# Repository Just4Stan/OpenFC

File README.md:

# OpenFC

Open-source Betaflight flight controller with integrated break-off ELRS receiver, based on the RP2354A microcontroller.

## Features

### Microcontroller
- **RP2354B** - Raspberry Pi dual-core ARM Cortex-M33 @ 150MHz (with integrated flash)

### Integrated ELRS Receiver (Break-off)
- On-board 2.4GHz ExpressLRS receiver module
- Break-off design allows for different placement if needed

### Sensors
- **IMU**: LSM6DSV16XTR 
- **Barometer**: BMI388

### Blackbox Data Logging
- **W25Q128JVPIQTR** - 128Mbit (16MB)

### Motor Outputs
- 4x PWM/DShot motor outputs

### Analog OSD on PIO
Hardware implementation of opamp and mux to detect syncs and select between white and black pixels. Needs software implementation still.

### Connectivity
- **USB-C** - Configuration and firmware flashing
- **UART0** - Serial RX/TX (ELRS connection pads)
- **UART1** - Spare serial port
- **PIO UART** - Software UART via RP2350 PIO (2x)
- **I2C** - External sensor expansion
- **SPI** - IMU and Blackbox on isolated bus.

### Analog Inputs
- Current sensor input (ADC)
- RSSI input (ADC)
- 1 external available ADC input

### Additional Features
- Addressable LED strip output (WS2812/NeoPixel)
- Buzzer output
- 16 LED's built in on corners
- ELRS ESP flashable by the RP2354B (BOOT/EN pins connected)

### Power
- 2S-6S batteries
- 10V and 5V regulated outputs, 10V is switchable.

## Repository Structure

```
OpenFC/
├── README.md
├── .gitignore
├── hardware/          ← KiCad project, libraries, and production files
│   ├── OpenFC.kicad_pro
│   ├── *.kicad_sch    ← Hierarchical schematics
│   ├── OpenFC.kicad_pcb
│   ├── lib.kicad_sym  ← Custom symbol library
│   ├── lib.pretty/    ← Custom footprint library
│   ├── lib.3dshapes/  ← 3D models
│   ├── production/    ← Gerbers, BOM, positions (all versions)
│   └── tools/         ← Analysis scripts
└── images/            ← Board renders
```

## Schematic Hierarchy

- `OpenFC.kicad_sch` - Top-level schematic
- `rp2350a.kicad_sch` - RP2354B microcontroller and supporting circuitry
- `elrs.kicad_sch` - ELRS 2.4GHz receiver module (break-off section)
- `Radioschematic.kicad_sch` - Radio/RF detailed schematic
- `power.kicad_sch` - Power supply and regulation
- `imu.kicad_sch` - LSM6DSV16XTR IMU
- `baro.kicad_sch` - BMP388 barometer
- `compass.kicad_sch` - LIS3MDLTR magnetometer (not populated, but there's space for it)
- `blackbox.kicad_sch` - W25Q128 flash memory
- `leds.kicad_sch` - Status LEDs
- `osd.kicad_sch` - OSD circuitry
- `connectors.kicad_sch` - External connectors
- `pads.kicad_sch` - Solder pads and test points

## Design Files

This project uses **KiCad 9.0** for schematic and PCB design. All symbol, footprint, and 3D model libraries are included in the repository — no external library setup is required.

## License

This project is open-source hardware. See LICENSE file for details.

## Contributing

Contributions are welcome! Please open an issue or submit a pull request.

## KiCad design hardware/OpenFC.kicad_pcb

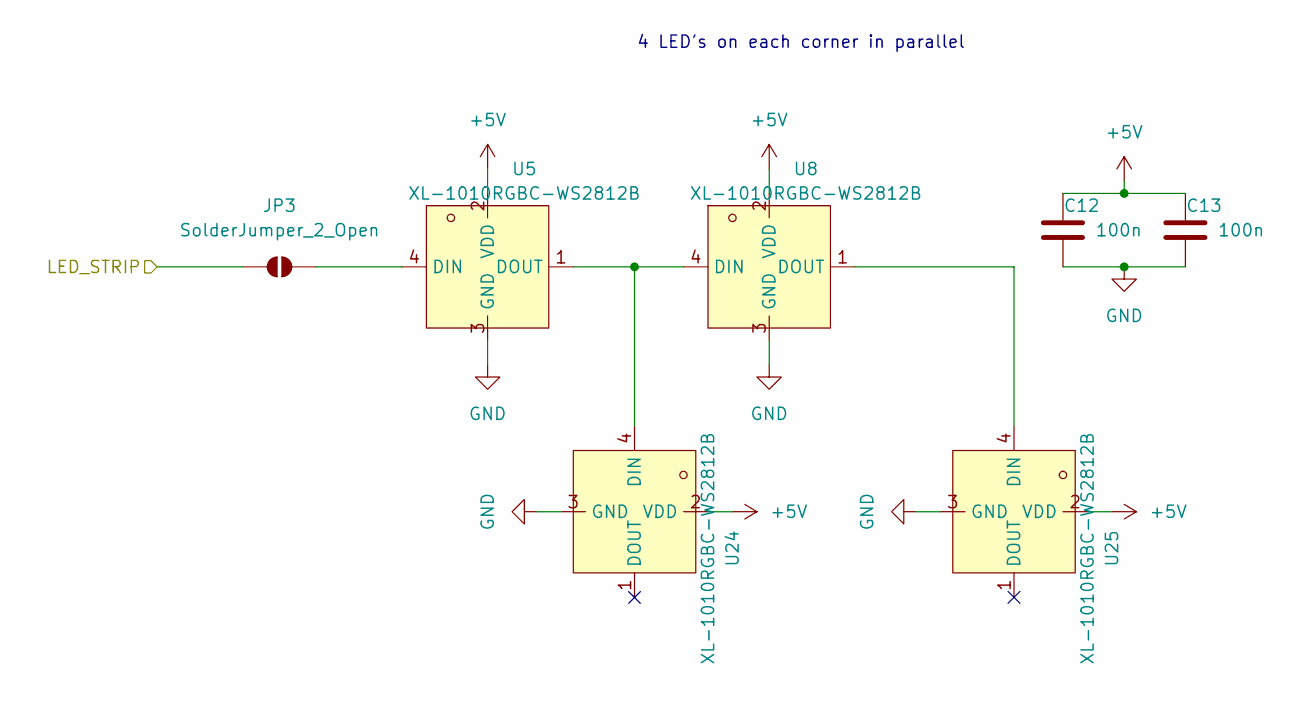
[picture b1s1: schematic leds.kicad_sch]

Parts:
C12, C13: 100n; C_0201_0603Metric; LCSC C76939
JP3: SolderJumper_2_Open; MouseBite-Slot-Jumper_0201
U5, U8, U24, U25: XL-1010RGBC-WS2812B; LED-SMD_4P-L1.0-W1.0-TL_XL-1010RGBC-WS2812B; LCSC Part C5349953

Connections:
+5V: C12.1, C13.1, U5.2 (VDD), U8.2 (VDD), U24.2 (VDD), U25.2 (VDD); also elsewhere on the board
/LED: JP3.1 (A); also elsewhere on the board
unnamed: JP3.2 (B), U5.4 (DIN)
unnamed: U5.1 (DOUT), U8.4 (DIN), U24.4 (DIN)
unnamed: U8.1 (DOUT), U25.4 (DIN)

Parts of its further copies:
C18, C19, C46, C47, C57, C58: 100n; C_0201_0603Metric; LCSC C76939
JP1, JP2, JP4: SolderJumper_2_Open; MouseBite-Slot-Jumper_0201
U3, U4, U15, U16, U17, U18, U22, U23, U26, U27, U28, U29: XL-1010RGBC-WS2812B; LED-SMD_4P-L1.0-W1.0-TL_XL-1010RGBC-WS2812B; LCSC Part C5349953

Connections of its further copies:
+5V: C18.1, C19.1, C46.1, C47.1, C57.1, C58.1, U3.2 (VDD), U4.2 (VDD), U15.2 (VDD), U16.2 (VDD), U17.2 (VDD), U18.2 (VDD), U22.2 (VDD), U23.2 (VDD), U26.2 (VDD), U27.2 (VDD), U28.2 (VDD), U29.2 (VDD); also elsewhere on the board
/LED: JP1.1 (A), JP2.1 (A), JP4.1 (A); also elsewhere on the board
unnamed: JP1.2 (B), U3.4 (DIN)
unnamed: JP2.2 (B), U17.4 (DIN)
unnamed: JP4.2 (B), U26.4 (DIN)
unnamed: U3.1 (DOUT), U4.4 (DIN), U15.4 (DIN)
unnamed: U15.1 (DOUT), U16.4 (DIN)
unnamed: U17.1 (DOUT), U18.4 (DIN), U22.4 (DIN)
unnamed: U22.1 (DOUT), U23.4 (DIN)
unnamed: U26.1 (DOUT), U27.4 (DIN), U28.4 (DIN)
unnamed: U28.1 (DOUT), U29.4 (DIN)

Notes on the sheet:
4 LED's on each corner in parallel

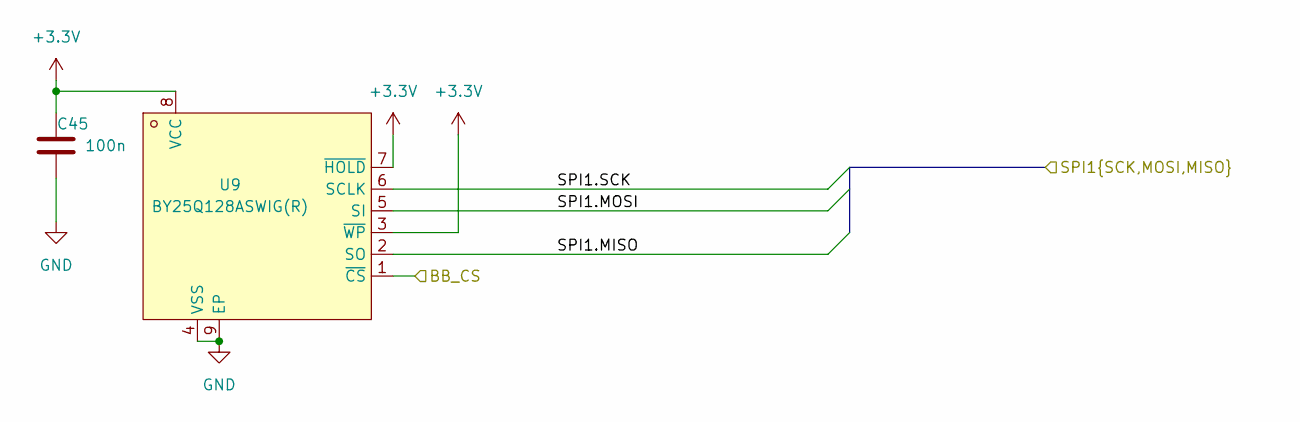
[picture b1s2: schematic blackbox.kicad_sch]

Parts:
C45: 100n; C_0201_0603Metric; LCSC C76939
U9: BY25Q128ASWIG(R); WSON-8_L6.0-W5.0-P1.27-BL-EP; LCSC Part C394872

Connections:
+3.3V: C45.1, U9.3 (~WP), U9.7 (~HOLD), U9.8 (VCC); also elsewhere on the board
/BLACKBOX/BB_CS: U9.1 (~CS); also elsewhere on the board
/BLACKBOX/SPI1.MISO: U9.2 (SO); also elsewhere on the board
/BLACKBOX/SPI1.MOSI: U9.5 (SI); also elsewhere on the board
/BLACKBOX/SPI1.SCK: U9.6 (SCLK); also elsewhere on the board

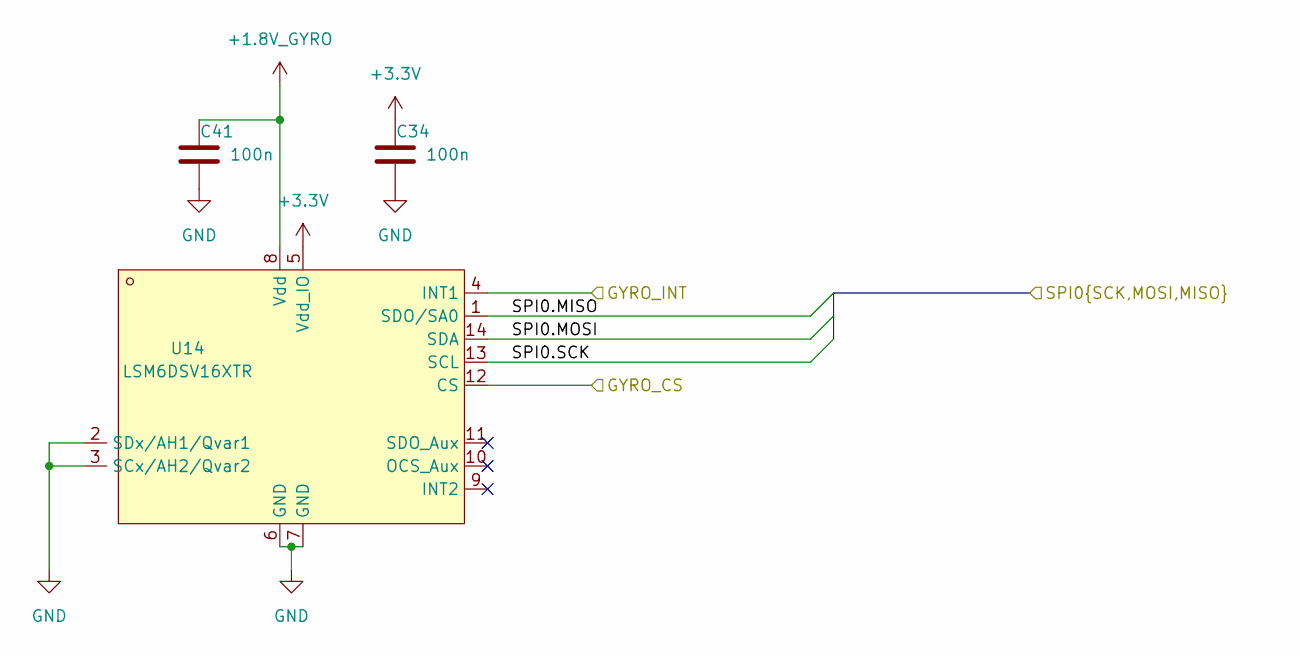
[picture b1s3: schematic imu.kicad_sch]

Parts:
C34, C41: 100n; C_0201_0603Metric; LCSC C76939
U14: LSM6DSV16XTR; LGA-14_L3.0-W2.5-P0.50-BR; LCSC Part C5267406

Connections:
+1.8V_GYRO: C41.1, U14.8 (Vdd); also elsewhere on the board
+3.3V: C34.1, U14.5 (Vdd_IO); also elsewhere on the board
/IMU/GYRO_CS: U14.12 (CS); also elsewhere on the board
/IMU/GYRO_INT: U14.4 (INT1); also elsewhere on the board
/IMU/SPI0.MISO: U14.1 (SDO/SA0); also elsewhere on the board
/IMU/SPI0.MOSI: U14.14 (SDA); also elsewhere on the board
/IMU/SPI0.SCK: U14.13 (SCL); also elsewhere on the board

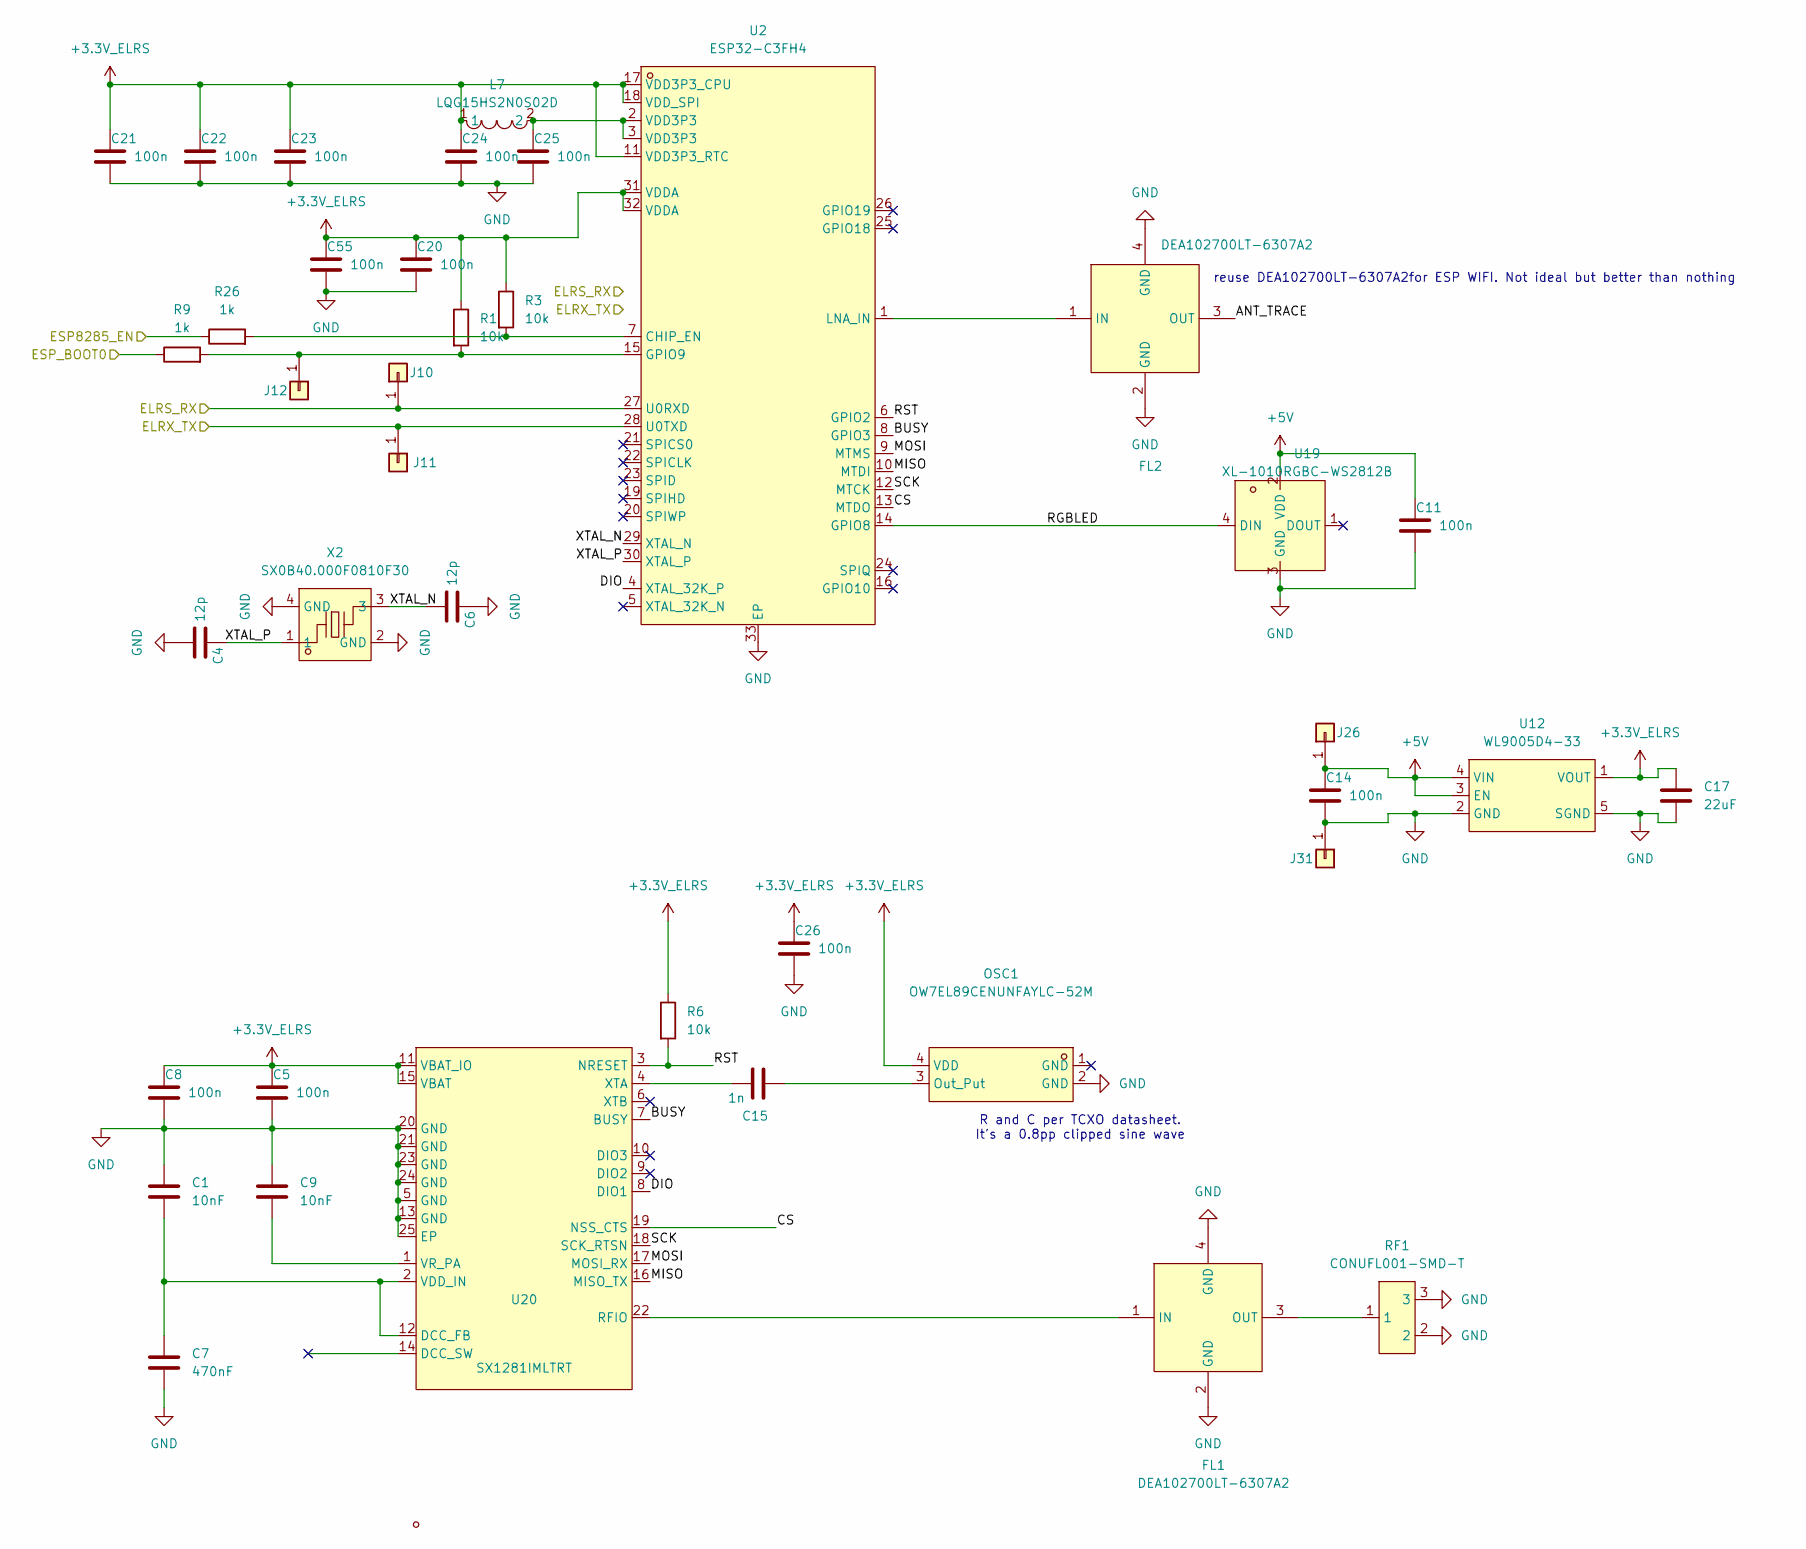
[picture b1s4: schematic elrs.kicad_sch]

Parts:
C1, C9: 10nF; C_0201_0603Metric; LCSC C76941
C4, C6: 12p; C_0201_0603Metric; LCSC C161404
C5, C8, C11, C14, C20, C21, C22, C23, C24, C25, C26, C55: 100n; C_0201_0603Metric; LCSC C76939
C7: 470nF; C_0201_0603Metric; LCSC C85926
C15: 1n; C_0201_0603Metric; LCSC C85934
C17: 22uF; C_0402_1005Metric; LCSC C105226
FL1, FL2: DEA102700LT-6307A2; FILTER-SMD_4P-L1.0-W0.5-L; LCSC Part C574024
J10, J11, J12, J26, J31: 5V; small_pad
L7: LQG15HS2N0S02D; L0402; LCSC Part C18216
OSC1: OW7EL89CENUNFAYLC-52M; OSC-SMD_4P-L2.0-W1.6-BL_TXC_7Z; LCSC Part C22434896
R1, R3, R6: 10k; C_0201_0603Metric; LCSC C473048
R9, R26: 1k; C_0201_0603Metric; LCSC C270365
RF1: CONUFL001-SMD-T; IPEX-SMD_3P-L2.6-W2.6-LS3.0; LCSC Part C22418213
U2: ESP32-C3FH4; QFN-32_L5.0-W5.0-P0.50-TL-EP3.7; LCSC Part C2858491
U12: WL9005D4-33; UDFN-4_L1.0-W1.0-P0.65-TL; LCSC Part C5357206
U19: XL-1010RGBC-WS2812B; LED-SMD_4P-L1.0-W1.0-TL_XL-1010RGBC-WS2812B; LCSC Part C5349953
U20: SX1281IMLTRT; QFN-24_L4.0-W4.0-P0.50-TL-EP2.6; LCSC Part C2151551
X2: SX0B40.000F0810F30; CRYSTAL-SMD_4P-L1.6-W1.2-BL; LCSC Part C7301926

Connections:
+3.3V_ELRS: C5.1, C8.1, C17.1, C20.1, C21.1, C22.1, C23.1, C24.1, C26.1, C55.1, L7.1, OSC1.4 (VDD), R1.1, R3.1, R6.1, U2.11 (VDD3P3_RTC), U2.17 (VDD3P3_CPU), U2.18 (VDD_SPI), U2.31 (VDDA), U2.32 (VDDA), U12.1 (VOUT), U20.11 (VBAT_IO), U20.15 (VBAT)
+5V: C11.1, C14.1, J26.1, U12.3 (EN), U12.4 (VIN), U19.2 (VDD); also elsewhere on the board
/ELRS/ANT_TRACE: FL2.3 (OUT)
/ELRS/BUSY: U2.8 (GPIO3), U20.7 (BUSY)
/ELRS/CS: U2.13 (MTDO), U20.19 (NSS_CTS)
/ELRS/DIO: U2.4 (XTAL_32K_P), U20.8 (DIO1)
/ELRS/ESP8285_EN: R26.1; also elsewhere on the board
/ELRS/ESP_BOOT0: R9.1; also elsewhere on the board
/ELRS/MISO: U2.10 (MTDI), U20.16 (MISO_TX)
/ELRS/MOSI: U2.9 (MTMS), U20.17 (MOSI_RX)
/ELRS/RGBLED: U2.14 (GPIO8), U19.4 (DIN)
/ELRS/RST: R6.2, U2.6 (GPIO2), U20.3 (NRESET)
/ELRS/SCK: U2.12 (MTCK), U20.18 (SCK_RTSN)
/ELRS/XTAL_N: C6.2, U2.29 (XTAL_N), X2.3
/ELRS/XTAL_P: C4.1, U2.30 (XTAL_P), X2.1
/UART1_RX: J11.1, U2.28 (U0TXD); also elsewhere on the board
/UART1_TX: J10.1, U2.27 (U0RXD); also elsewhere on the board
unnamed: C25.1, L7.2, U2.2 (VDD3P3), U2.3 (VDD3P3)
unnamed: FL1.1 (IN), U20.22 (RFIO)
unnamed: FL1.3 (OUT), RF1.1
unnamed: FL2.1 (IN), U2.1 (LNA_IN)
unnamed: J12.1, R1.2, R9.2, U2.15 (GPIO9)
unnamed: C15.2, OSC1.3 (Out_Put)
unnamed: R3.2, R26.2, U2.7 (CHIP_EN)
unnamed: C1.2, C7.1, U20.2 (VDD_IN), U20.12 (DCC_FB)
unnamed: C9.2, U20.1 (VR_PA)
unnamed: C15.1, U20.4 (XTA)

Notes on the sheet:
reuse DEA102700LT-6307A2for ESP WIFI. Not ideal but better than nothing
R and C per TCXO datasheet. It's a 0.8pp clipped sine wave

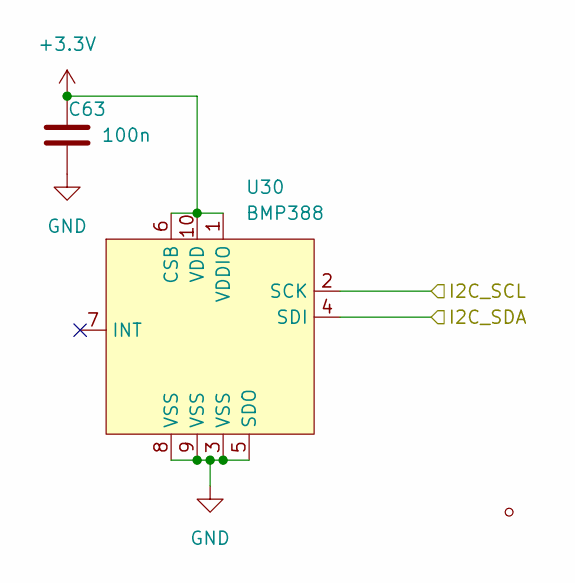
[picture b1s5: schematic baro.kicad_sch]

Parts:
C63: 100n; C_0201_0603Metric; LCSC C76939
U30: BMP388; SENSORM-SMD_BMP388; LCSC Part C779278

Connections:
+3.3V: C63.1, U30.1 (VDDIO), U30.6 (CSB), U30.10 (VDD); also elsewhere on the board
/I2C_SCL: U30.2 (SCK); also elsewhere on the board
/I2C_SDA: U30.4 (SDI); also elsewhere on the board

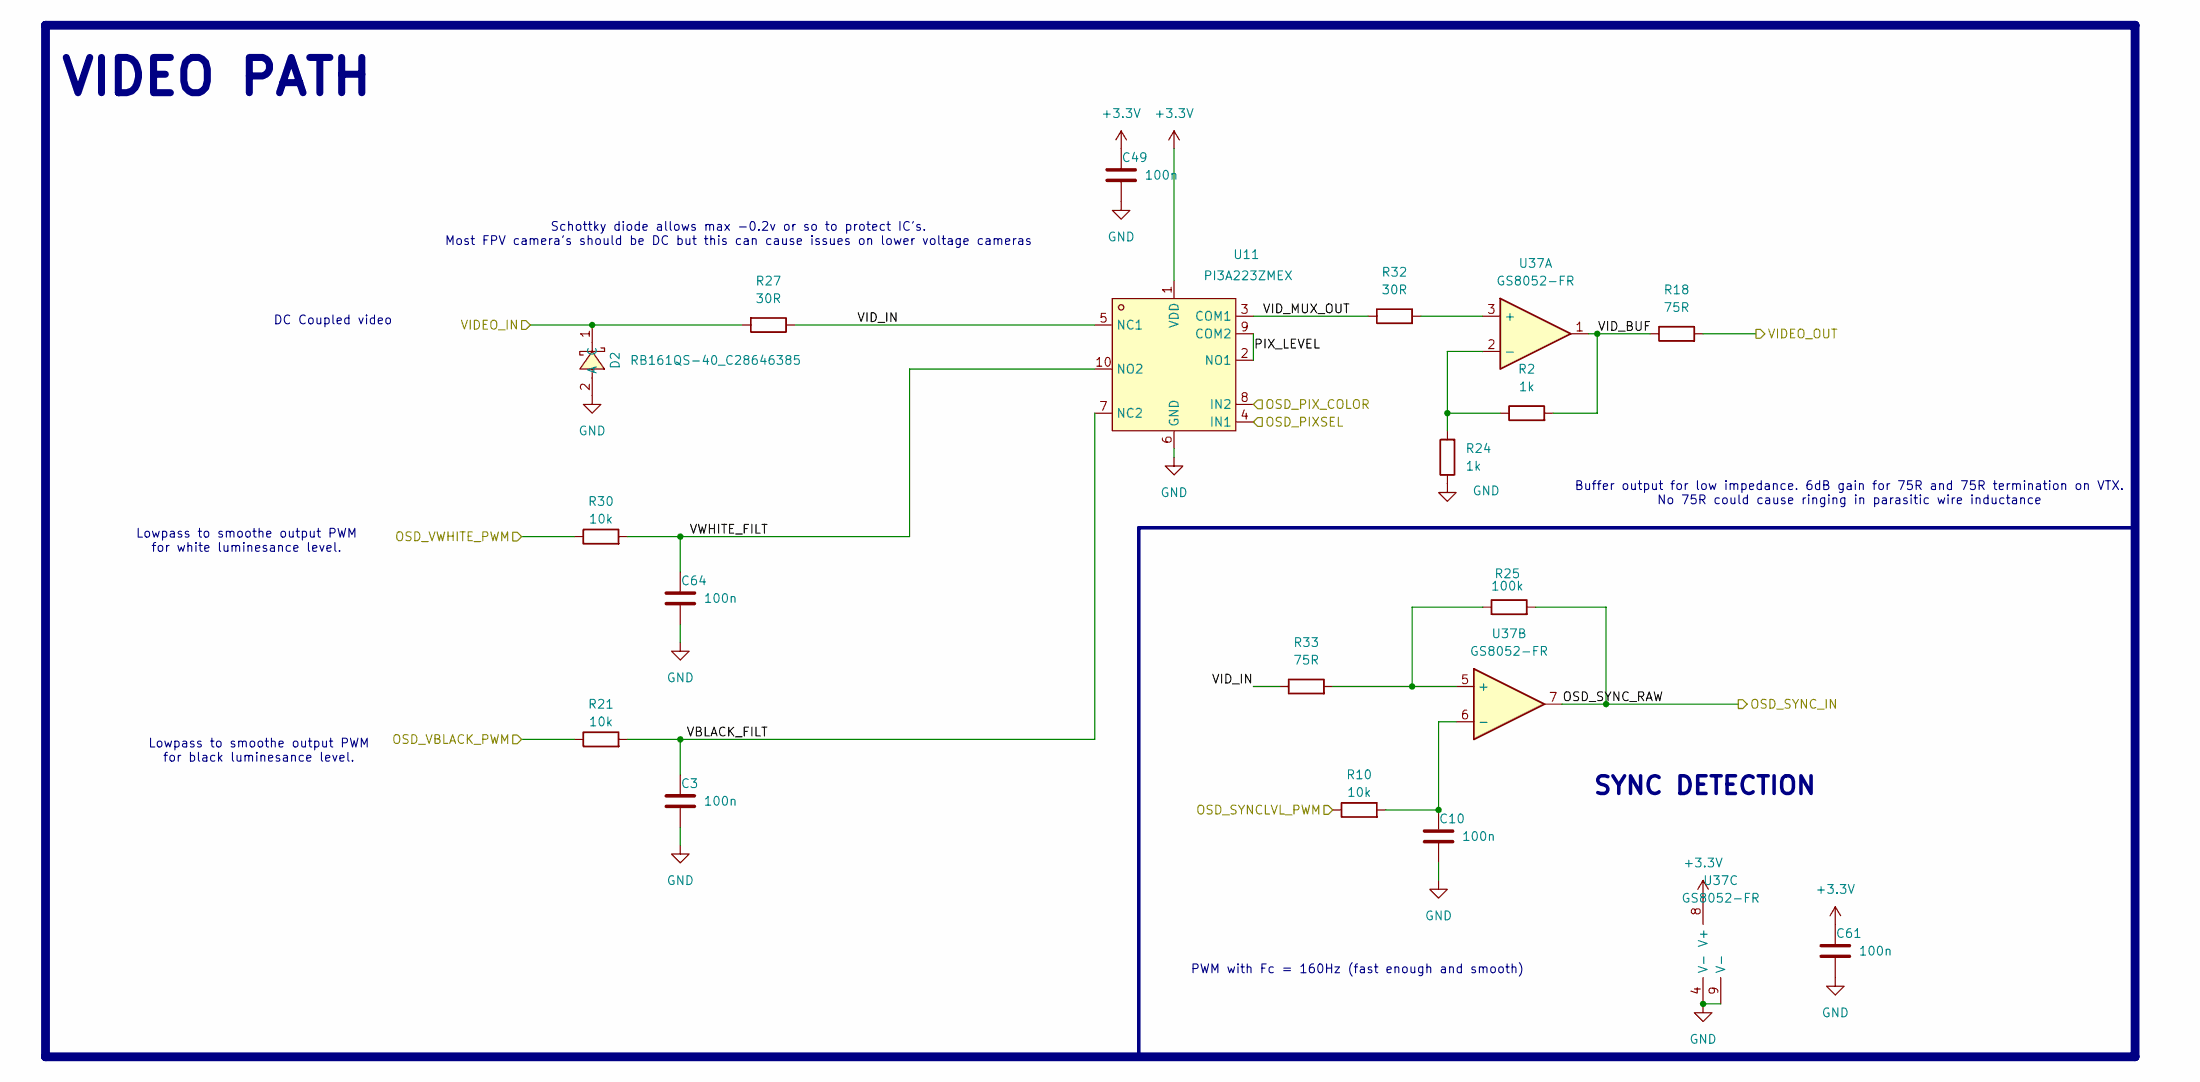
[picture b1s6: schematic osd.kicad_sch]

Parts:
C3, C10, C49, C61, C64: 100n; C_0201_0603Metric; LCSC C76939
D2: RB161QS-40_C28646385; SOD-882_L1.0-W0.6-RD; LCSC Part C28646385
R2, R24: 1k; C_0201_0603Metric; LCSC C270365
R10, R21, R30: 10k; C_0201_0603Metric; LCSC C473048
R18, R33: 75R; C_0201_0603Metric; LCSC C473570
R25: 100k; C_0201_0603Metric; LCSC C270364
R27, R32: 30R; C_0201_0603Metric; LCSC C778391
U11: PI3A223ZMEX; UQFN-10_L1.8-W1.4-P0.40-TL; LCSC Part C2673436
U37: GS8052-FR; WSON-8-1EP_2x2mm_P0.5mm_EP0.9x1.6mm; LCSC C605423

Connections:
+3.3V: C49.1, C61.1, U11.1 (VDD), U37.8 (V+); also elsewhere on the board
/OSD/OSD_PIXSEL: U11.4 (IN1); also elsewhere on the board
/OSD/OSD_PIX_COLOR: U11.8 (IN2); also elsewhere on the board
/OSD/OSD_SYNCLVL_PWM: R10.1; also elsewhere on the board
/OSD/OSD_SYNC_RAW: R25.2, U37.7; also elsewhere on the board
/OSD/OSD_VBLACK_PWM: R21.1; also elsewhere on the board
/OSD/OSD_VWHITE_PWM: R30.1; also elsewhere on the board
/OSD/PIX_LEVEL: U11.2 (NO1), U11.9 (COM2)
/OSD/VBLACK_FILT: C3.1, R21.2, U11.7 (NC2)
/OSD/VIDEO_IN: D2.1 (C), R27.2; also elsewhere on the board
/OSD/VIDEO_OUT: R18.2; also elsewhere on the board
/OSD/VID_BUF: R2.2, R18.1, U37.1
/OSD/VID_IN: R27.1, R33.1, U11.5 (NC1)
/OSD/VID_MUX_OUT: R32.1, U11.3 (COM1)
/OSD/VWHITE_FILT: C64.1, R30.2, U11.10 (NO2)
unnamed: R32.2, U37.3 (+)
unnamed: R2.1, R24.2, U37.2 (-)
unnamed: R25.1, R33.2, U37.5 (+)
unnamed: C10.1, R10.2, U37.6 (-)

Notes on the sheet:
PWM with Fc = 160Hz (fast enough and smooth)
DC Coupled video
Buffer output for low impedance. 6dB gain for 75R and 75R termination on VTX. No 75R could cause ringing in parasitic wire inductance
VIDEO PATH
SYNC DETECTION
Lowpass to smoothe output PWM for white luminesance level.
Lowpass to smoothe output PWM for black luminesance level.
Schottky diode allows max -0.2v or so to protect IC's. Most FPV camera's should be DC but this can cause issues on lower voltage cameras

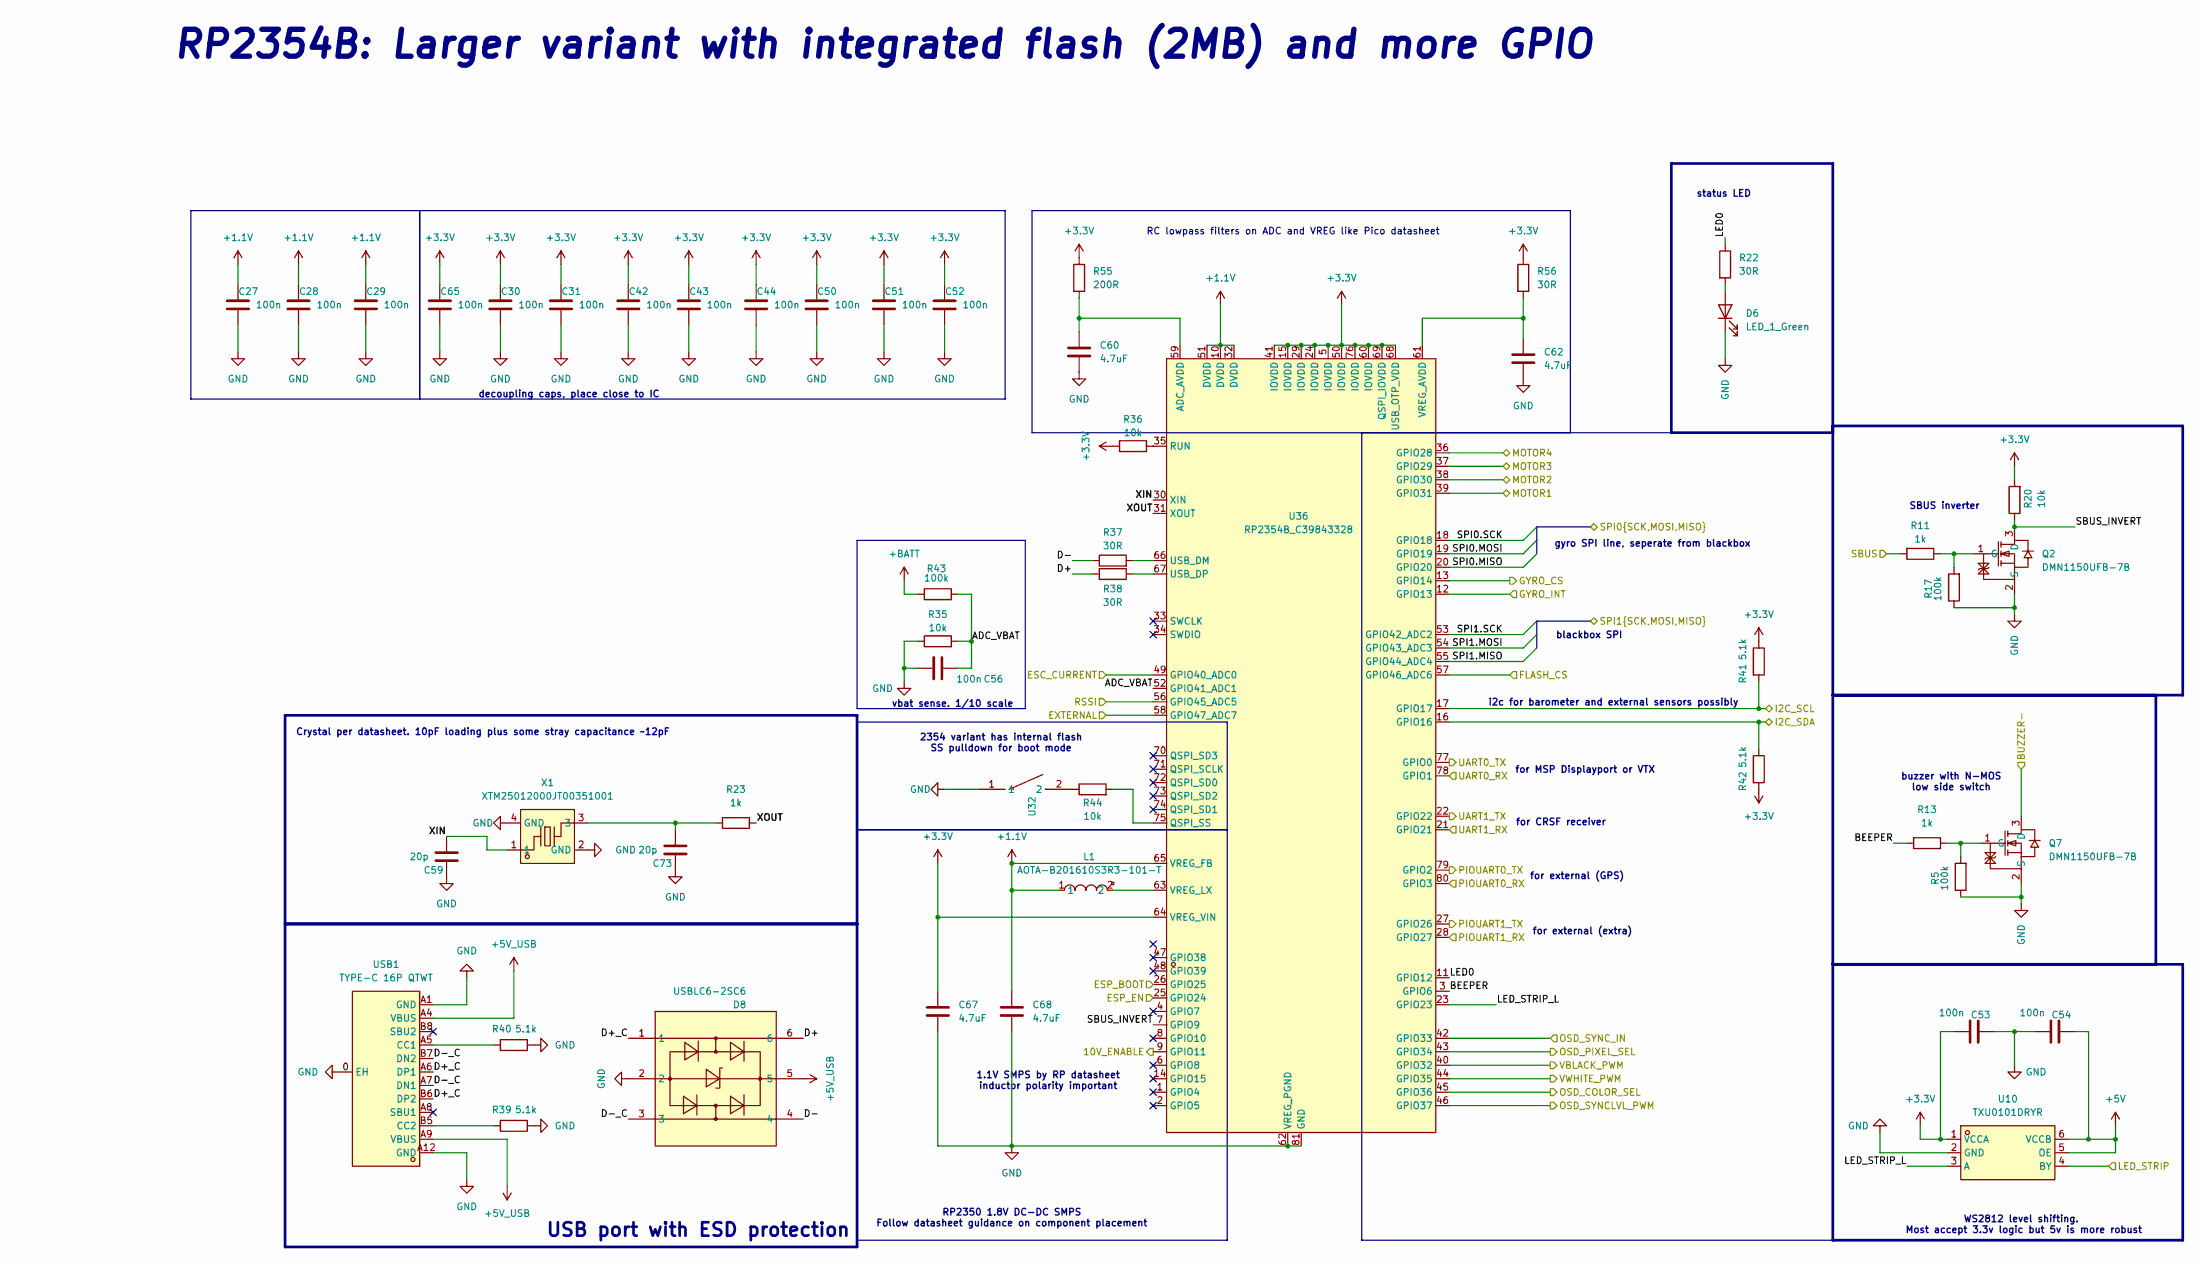
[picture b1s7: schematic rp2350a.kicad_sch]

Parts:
C27, C28, C29, C30, C31, C42, C43, C44, C50, C51, C52, C53, C54, C56, C65: 100n; C_0201_0603Metric; LCSC C76939
C59, C73: 20p; C_0201_0603Metric; LCSC C76923
C60, C62, C67, C68: 4.7uF; C_0402_1005Metric; LCSC C23733
D6: LED_1_Green; LED_0603_1608Metric; LCSC C2994781
D8: USBLC6-2SC6; SOT-666; LCSC Part C7519
L1: AOTA-B201610S3R3-101-T; IND-SMD_L2.0-W1.6_AOTA-B201610S3R3-101-T; LCSC Part C42411119
Q2, Q7: DMN1150UFB-7B; DFN-3L_L1.0-W0.6-P0.65-BR; LCSC Part C459538
R5, R17, R43: 100k; C_0201_0603Metric; LCSC C270364
R11, R13, R23: 1k; C_0201_0603Metric; LCSC C270365
R20, R35, R36, R44: 10k; C_0201_0603Metric; LCSC C473048
R22, R37, R38, R56: 30R; C_0201_0603Metric; LCSC C778391
R39, R40, R41, R42: 5.1k; C_0201_0603Metric; LCSC C270344
R55: 200R; C_0201_0603Metric; LCSC C270359
U10: TXU0101DRYR; SON-6_L1.5-W1.0-P0.50-TL; LCSC Part C5217869
U32: TS2306A 240GF MSM 9_C2976675; SW-SMD_4P-L3.0-W2.0-P0.85-LS3.5; LCSC Part C2976675
U36: RP2354B_C39843328; QFN-80_L10.0-W10.0-P0.40-TL-EP3.4; LCSC Part C39843328
USB1: TYPE-C 16P QTWT; USB-TYPE-C-SMD_TYPE-C-16P-QTWT; LCSC Part C5187472
X1: XTM25012000JT00351001; CRYSTAL-SMD_4P-L2.5-W2.0-BL-A; LCSC Part C37635340

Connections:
+1.1V: C27.1, C28.1, C29.1, C68.1, L1.1, U36.10 (DVDD), U36.32 (DVDD), U36.51 (DVDD), U36.65 (VREG_FB)
+3.3V: C30.1, C31.1, C42.1, C43.1, C44.1, C50.1, C51.1, C52.1, C53.1, C65.1, C67.1, R20.2, R36.1, R41.1, R42.2, R55.1, R56.1, U10.1 (VCCA), U36.5 (IOVDD), U36.15 (IOVDD), U36.24 (IOVDD), U36.29 (IOVDD), U36.41 (IOVDD), U36.50 (IOVDD), U36.60 (IOVDD), U36.64 (VREG_VIN), U36.68 (USB_OTP_VDD), U36.69 (QSPI_IOVDD), U36.76 (IOVDD); also elsewhere on the board
+5V: C54.2, U10.5 (OE), U10.6 (VCCB); also elsewhere on the board
+5V_USB: D8.5, USB1.A4 (VBUS), USB1.A9 (VBUS); also elsewhere on the board
+BATT: R43.1; also elsewhere on the board
/BLACKBOX/BB_CS: U36.57 (GPIO46_ADC6); also elsewhere on the board
/BLACKBOX/SPI1.MISO: U36.55 (GPIO44_ADC4); also elsewhere on the board
/BLACKBOX/SPI1.MOSI: U36.54 (GPIO43_ADC3); also elsewhere on the board
/BLACKBOX/SPI1.SCK: U36.53 (GPIO42_ADC2); also elsewhere on the board
/ELRS/ESP8285_EN: U36.25 (GPIO24); also elsewhere on the board
/ELRS/ESP_BOOT0: U36.26 (GPIO25); also elsewhere on the board
/I2C_SCL: R41.2, U36.17 (GPIO17); also elsewhere on the board
/I2C_SDA: R42.1, U36.16 (GPIO16); also elsewhere on the board
/IMU/GYRO_CS: U36.13 (GPIO14); also elsewhere on the board
/IMU/GYRO_INT: U36.12 (GPIO13); also elsewhere on the board
/IMU/SPI0.MISO: U36.20 (GPIO20); also elsewhere on the board
/IMU/SPI0.MOSI: U36.19 (GPIO19); also elsewhere on the board
/IMU/SPI0.SCK: U36.18 (GPIO18); also elsewhere on the board
/LED: U10.4 (BY); also elsewhere on the board
/OSD/OSD_PIXSEL: U36.43 (GPIO34); also elsewhere on the board
/OSD/OSD_PIX_COLOR: U36.45 (GPIO36); also elsewhere on the board
/OSD/OSD_SYNCLVL_PWM: U36.46 (GPIO37); also elsewhere on the board
/OSD/OSD_SYNC_RAW: U36.42 (GPIO33); also elsewhere on the board
/OSD/OSD_VBLACK_PWM: U36.40 (GPIO32); also elsewhere on the board
/OSD/OSD_VWHITE_PWM: U36.44 (GPIO35); also elsewhere on the board
/PADS/ADC2: U36.58 (GPIO47_ADC7); also elsewhere on the board
/PADS/BUZZER-: Q7.3 (D); also elsewhere on the board
/PADS/CURRENT: U36.49 (GPIO40_ADC0); also elsewhere on the board
/PADS/DIGITAL_RX: U36.78 (GPIO1); also elsewhere on the board
/PADS/DIGITAL_TX: U36.77 (GPIO0); also elsewhere on the board
/PADS/M1: U36.39 (GPIO31); also elsewhere on the board
/PADS/M2: U36.38 (GPIO30); also elsewhere on the board
/PADS/M3: U36.37 (GPIO29); also elsewhere on the board
/PADS/M4: U36.36 (GPIO28); also elsewhere on the board
/PADS/PIOUART0_RX: U36.80 (GPIO3); also elsewhere on the board
/PADS/PIOUART0_TX: U36.79 (GPIO2); also elsewhere on the board
/PADS/PIOUART1_RX: U36.28 (GPIO27); also elsewhere on the board
/PADS/PIOUART1_TX: U36.27 (GPIO26); also elsewhere on the board
/PADS/RSSI: U36.56 (GPIO45_ADC5); also elsewhere on the board
/PADS/SBUS: R11.2; also elsewhere on the board
/POWER/10V_ENABLE: U36.9 (GPIO11); also elsewhere on the board
/RP2350A/ADC_VBAT: C56.2, R35.2, R43.2, U36.52 (GPIO41_ADC1)
/RP2350A/BEEPER: R13.2, U36.3 (GPIO6)
/RP2350A/D+: D8.6, R38.2
/RP2350A/D+_C: D8.1, USB1.A6 (DP1), USB1.B6 (DP2)
/RP2350A/D-: D8.4, R37.1
/RP2350A/D-_C: D8.3, USB1.A7 (DN1), USB1.B7 (DN2)
/RP2350A/LED0: R22.1, U36.11 (GPIO12)
/RP2350A/LED_STRIP_L: U10.3 (A), U36.23 (GPIO23)
/RP2350A/SBUS_INVERT: Q2.3 (D), R20.1, U36.7 (GPIO9)
/RP2350A/XIN: C59.2, U36.30 (XIN), X1.1
/RP2350A/XOUT: R23.1, U36.31 (XOUT)
/UART1_RX: U36.21 (GPIO21); also elsewhere on the board
/UART1_TX: U36.22 (GPIO22); also elsewhere on the board
unnamed: C73.2, R23.2, X1.3
unnamed: D6.2 (A), R22.2
unnamed: Q2.1 (G), R11.1, R17.2
unnamed: Q7.1 (G), R5.2, R13.1
unnamed: R44.1, U32.2
unnamed: C60.1, R55.2, U36.59 (ADC_AVDD)
unnamed: R44.2, U36.75 (QSPI_SS)
unnamed: R36.2, U36.35 (RUN)
unnamed: R37.2, U36.66 (USB_DM)
unnamed: R38.1, U36.67 (USB_DP)
unnamed: C62.1, R56.2, U36.61 (VREG_AVDD)
unnamed: L1.2, U36.63 (VREG_LX)
unnamed: R40.2, USB1.A5 (CC1)
unnamed: R39.2, USB1.B5 (CC2)

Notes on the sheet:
vbat sense. 1/10 scale
RP2354B: Larger variant with integrated flash (2MB) and more GPIO
blackbox SPI
buzzer with N-MOS low side switch
for MSP Displayport or VTX
2354 variant has internal flash SS pulldown for boot mode
RP2350 1.8V DC-DC SMPS Follow datasheet guidance on component placement
for CRSF receiver
gyro SPI line, seperate from blackbox
decoupling caps, place close to IC
for external (extra)
status LED
Crystal per datasheet. 10pF loading plus some stray capacitance ~12pF
for external (GPS)
i2c for barometer and external sensors possibly
SBUS inverter
RC lowpass filters on ADC and VREG like Pico datasheet
WS2812 level shifting. Most accept 3.3v logic but 5v is more robust
USB port with ESD protection
1.1V SMPS by RP datasheet inductor polarity important

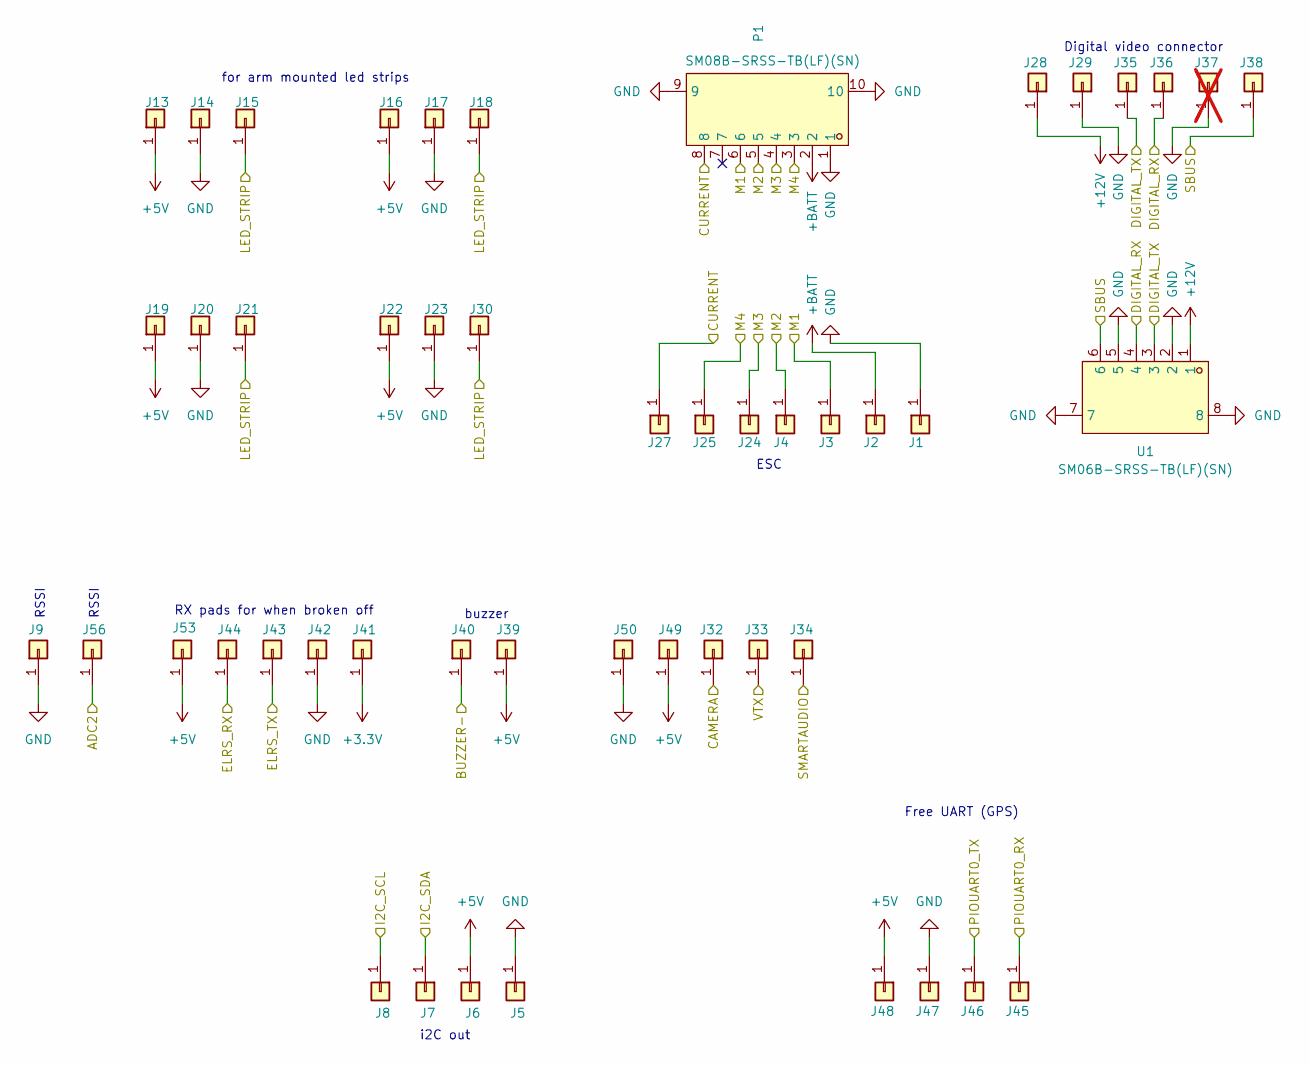
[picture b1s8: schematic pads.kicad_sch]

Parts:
J1, J2, J3, J4, J5, J6, J7, J8, J9, J13, J14, J15, J16, J17, J18, J19, J20, J21, J22, J23, J24, J25, J27, J28, J29, J30, J32, J33, J34, J35, J36, J38, J39, J40, J41, J42, J43, J44, J45, J46, J47, J48, J49, J50, J53, J56: 5V; small_pad
J37: 5V; small_pad; not fitted
P1: SM08B-SRSS-TB(LF)(SN); CONN-TH_SM08B-SRSS-TB-LF-SN; LCSC Part C160407
U1: SM06B-SRSS-TB(LF)(SN); CONN-SMD_SM06B-SRSS-TB-LF-SN; LCSC Part C160405

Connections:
+5V: J6.1, J13.1, J16.1, J19.1, J22.1, J34.1, J39.1, J48.1, J49.1, J53.1; also elsewhere on the board
+12V: J28.1, U1.1; also elsewhere on the board
+BATT: J2.1, P1.2; also elsewhere on the board
/I2C_SCL: J8.1; also elsewhere on the board
/I2C_SDA: J7.1; also elsewhere on the board
/LED: J15.1, J18.1, J21.1, J30.1; also elsewhere on the board
/OSD/VIDEO_IN: J32.1; also elsewhere on the board
/OSD/VIDEO_OUT: J33.1; also elsewhere on the board
/PADS/BUZZER-: J40.1; also elsewhere on the board
/PADS/CURRENT: J27.1, P1.8; also elsewhere on the board
/PADS/DIGITAL_RX: J36.1, U1.4; also elsewhere on the board
/PADS/DIGITAL_TX: J35.1, U1.3; also elsewhere on the board
/PADS/M1: J3.1, P1.6; also elsewhere on the board
/PADS/M2: J4.1, P1.5; also elsewhere on the board
/PADS/M3: J24.1, P1.4; also elsewhere on the board
/PADS/M4: J25.1, P1.3; also elsewhere on the board
/PADS/PIOUART0_RX: J45.1; also elsewhere on the board
/PADS/PIOUART0_TX: J46.1; also elsewhere on the board
/PADS/RSSI: J56.1; also elsewhere on the board
/PADS/SBUS: J38.1, U1.6; also elsewhere on the board
/UART1_RX: J44.1; also elsewhere on the board
/UART1_TX: J43.1; also elsewhere on the board

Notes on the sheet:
RSSI
Free UART (GPS)
i2C out
buzzer
RX pads for when broken off
ESC
Digital video connector
for arm mounted led strips
